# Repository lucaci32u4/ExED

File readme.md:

# Extended Digital Electronics laboratory

This laboratory is intended to be used as teaching material for the 6th Digital Electronics laboratory in the Faculty of Computer Science, Politehnica University of Bucharest.

This laboratory material presents the functioning of a shift register, a ring counter and a phase-locked loop. The following applications can be built:

 * A semaphore-like appliance using a ring counter
 * A clock divider
 * Phase-locked loop used to correct the pulse width of a fixed-frequency input signal
 * Clock multiplier bult using the phase-locked loop and clock divider
 * Linear feedback shift register - a random number generator using the shift register and XOR gate

## Version v0.1

A batch of 10 boards v0.01 were built. Seven of them were populated and tested in field, while three were kept for archieval purposes.

After teaching the extended laboratory to two groups, the following observations can be made:

 * Replace the XOR gate with a XNOR gate to eliminate the need to seed the LFSR. A XNOR gate would allow it to be self-seeding.
 * There are missing traces near the shift registers that need to be drawn. This issue was fixed by hand using wire on the first batch
 * Remove R36 to allow a much more dynamic range for the PLL.
 * Add LED to all clock inputs to allow better observation of the circuit.
 * Add reverse-polarity protection.

These flaws are planned to be fixed in version v0.2.

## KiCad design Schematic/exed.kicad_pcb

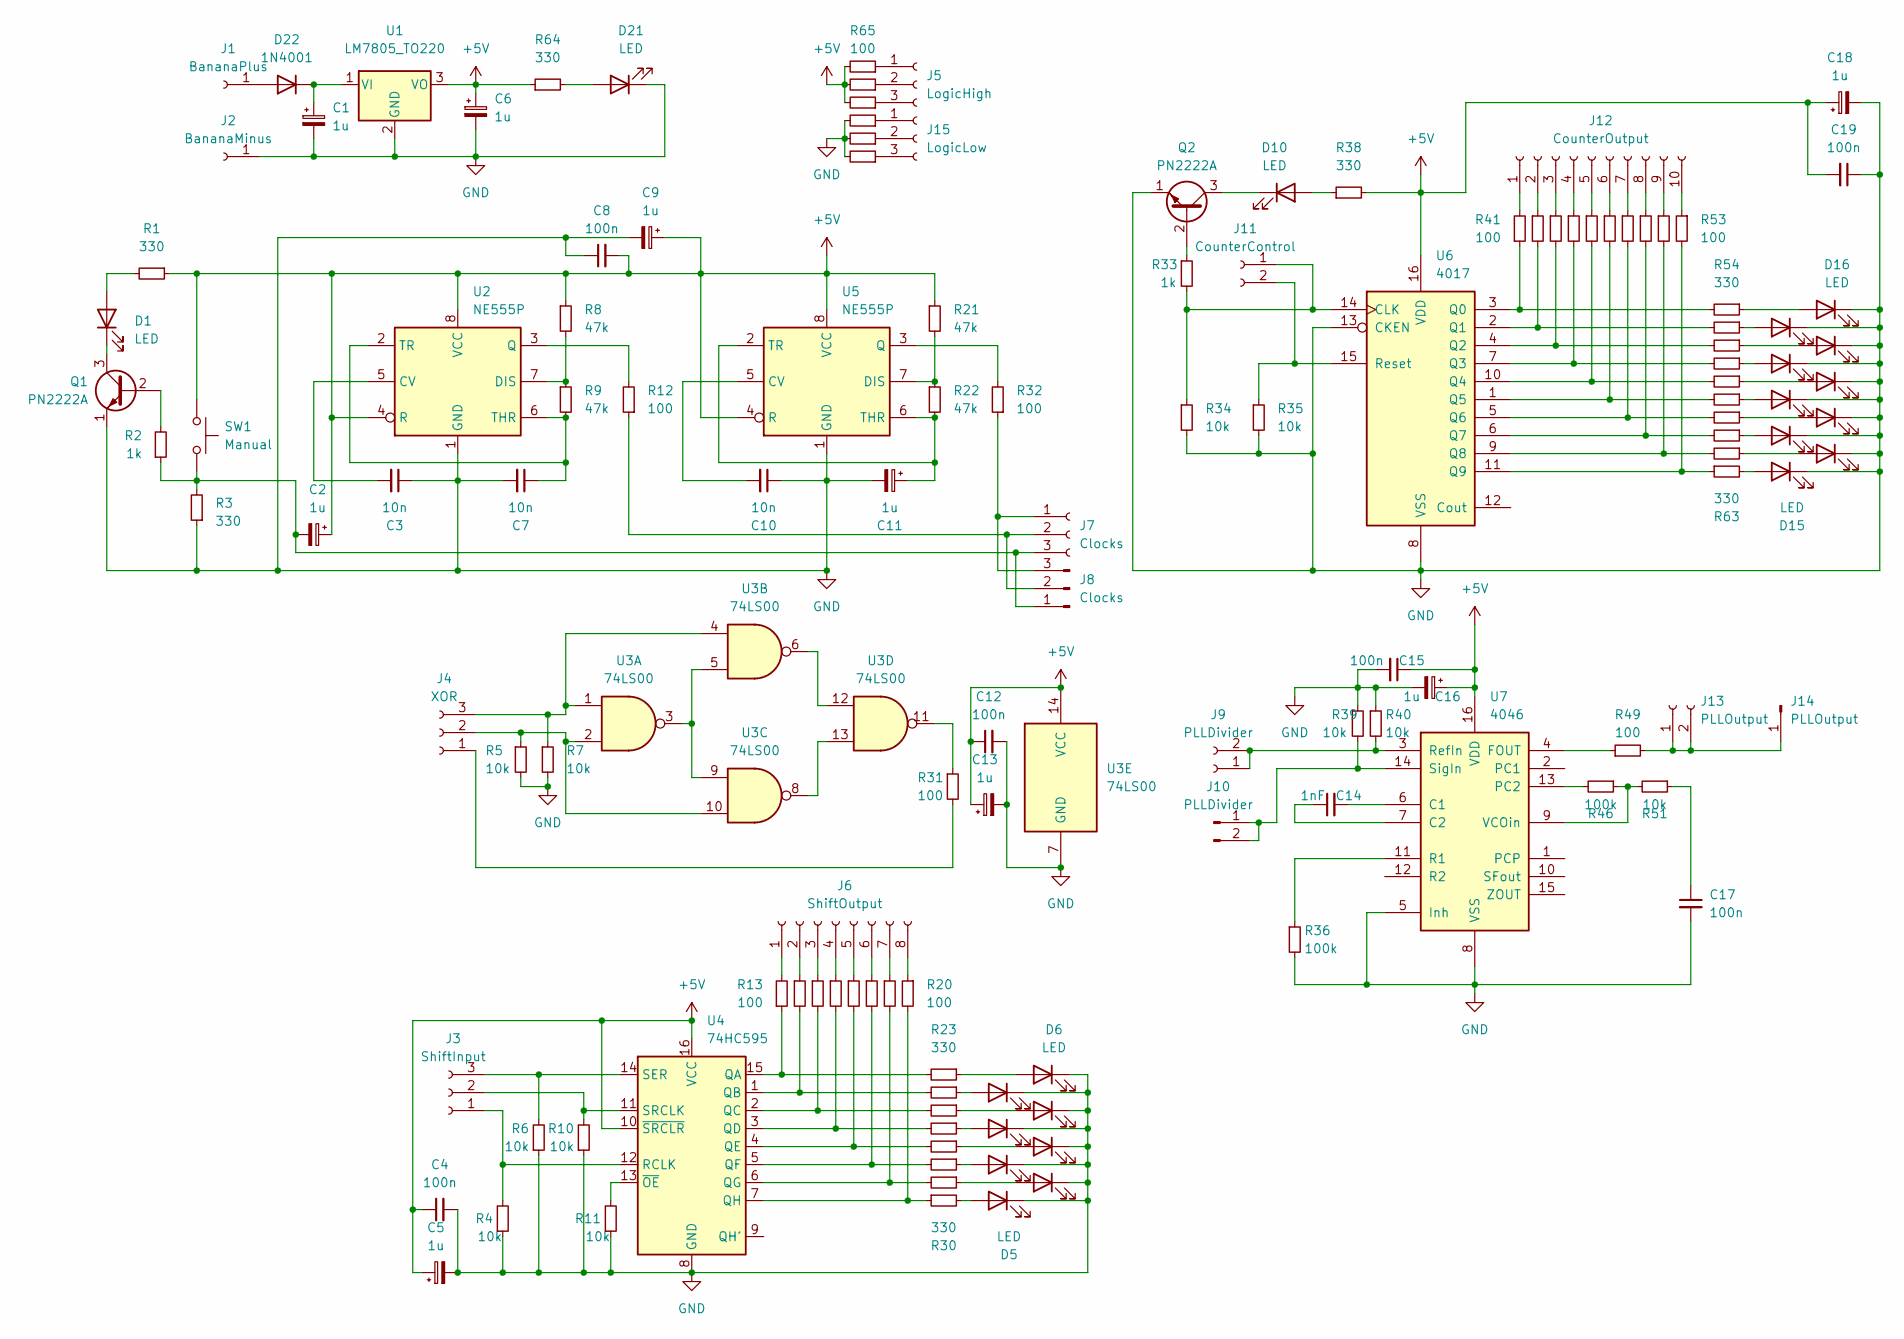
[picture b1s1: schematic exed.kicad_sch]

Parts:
C1, C2, C5, C6, C9, C11, C13, C16, C18: 1u; C_0603_1608Metric_Pad1.08x0.95mm_HandSolder
C3, C7, C10: 10n; C_0603_1608Metric_Pad1.08x0.95mm_HandSolder
C4, C8, C12, C15, C17, C19: 100n; C_0805_2012Metric_Pad1.18x1.45mm_HandSolder
C14: 1nF; C_0603_1608Metric_Pad1.08x0.95mm_HandSolder
D1, D2, D3, D4, D5, D6, D7, D8, D9, D10, D11, D12, D13, D14, D15, D16, D17, D18, D19, D20, D21: LED; LED_0603_1608Metric_Pad1.05x0.95mm_HandSolder
D22: 1N4001; D_DO-41_SOD81_P10.16mm_Horizontal
J1: BananaPlus; Banana_Jack_1Pin
J2: BananaMinus; Banana_Jack_1Pin
J3: ShiftInput; PinHeader_1x03_P2.54mm_Vertical
J4: XOR; PinHeader_1x03_P2.54mm_Vertical
J5: LogicHigh; PinHeader_1x03_P2.54mm_Vertical
J6: ShiftOutput; PinHeader_1x08_P2.54mm_Vertical
J7, J8: Clocks; PinHeader_1x03_P2.54mm_Vertical
J9, J10: PLLDivider; PinHeader_1x02_P2.54mm_Vertical
J11: CounterControl; PinHeader_1x02_P2.54mm_Vertical
J12: CounterOutput; PinHeader_1x10_P2.54mm_Vertical
J13: PLLOutput; PinHeader_1x02_P2.54mm_Vertical
J14: PLLOutput; PinHeader_1x01_P2.54mm_Vertical
J15: LogicLow; PinHeader_1x03_P2.54mm_Vertical
Q1, Q2: PN2222A; TO-92_Inline
R1, R3, R23, R24, R25, R26, R27, R28, R29, R30, R38, R54, R55, R56, R57, R58, R59, R60, R61, R62, R63, R64: 330; R_0603_1608Metric_Pad0.98x0.95mm_HandSolder
R2, R33: 1k; R_0603_1608Metric_Pad0.98x0.95mm_HandSolder
R4, R5, R6, R7, R10, R11, R34, R35, R39, R40, R51: 10k; R_0603_1608Metric_Pad0.98x0.95mm_HandSolder
R8, R9, R21, R22: 47k; R_0603_1608Metric_Pad0.98x0.95mm_HandSolder
R12, R13, R14, R15, R16, R17, R18, R19, R20, R31, R32, R41, R42, R43, R44, R45, R47, R48, R49, R50, R52, R53, R65, R66, R67, R68, R69, R70: 100; R_0603_1608Metric_Pad0.98x0.95mm_HandSolder
R36, R46: 100k; R_0603_1608Metric_Pad0.98x0.95mm_HandSolder
SW1: Manual; SW_PUSH_6mm
U1: LM7805_TO220; TO-220-3_Horizontal_TabDown
U2, U5: NE555P; DIP-8_W7.62mm
U3: 74LS00; DIP-14_W7.62mm
U4: 74HC595; DIP-16_W7.62mm
U6: 4017; DIP-16_W7.62mm
U7: 4046; DIP-16_W7.62mm

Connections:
+5V: C2.1, C4.1, C5.1, C6.1, C8.2, C9.1, C12.1, C13.1, C15.1, C16.1, C18.1, C19.2, R1.1, R8.1, R21.1, R38.2, R64.1, R65.2, R66.2, R67.2, SW1.1, U1.3 (VO), U2.4 (R), U2.8 (VCC), U3.14 (VCC), U4.10 (~SRCLR), U4.16 (VCC), U5.4 (R), U5.8 (VCC), U6.16 (VDD), U7.16 (VDD)
GND: C1.2, C3.1, C4.2, C5.2, C6.2, C7.2, C8.1, C9.2, C10.1, C11.2, C12.2, C13.2, C15.2, C16.2, C17.2, C18.2, C19.1, D2.1 (K), D3.1 (K), D4.1 (K), D5.1 (K), D6.1 (K), D7.1 (K), D8.1 (K), D9.1 (K), D11.1 (K), D12.1 (K), D13.1 (K), D14.1 (K), D15.1 (K), D16.1 (K), D17.1 (K), D18.1 (K), D19.1 (K), D20.1 (K), D21.1 (K), J2.1, Q1.1 (E), Q2.1 (E), R3.1, R4.1, R5.2, R6.1, R7.2, R10.1, R11.1, R34.2, R35.2, R36.2, R39.1, R40.1, R68.2, R69.2, R70.2, U1.2 (GND), U2.1 (GND), U3.7 (GND), U4.8 (GND), U5.1 (GND), U6.8 (VSS), U6.13 (CKEN), U7.5 (Inh), U7.8 (VSS)
unnamed: C17.1, R51.1
unnamed: D1.2 (A), R1.2
unnamed: D1.1 (K), Q1.3 (C)
unnamed: D2.2 (A), R24.1
unnamed: D3.2 (A), R26.1
unnamed: D4.2 (A), R28.1
unnamed: D5.2 (A), R30.2
unnamed: D6.2 (A), R23.1
unnamed: D7.2 (A), R25.1
unnamed: D8.2 (A), R27.1
unnamed: D9.2 (A), R29.1
unnamed: D10.2 (A), R38.1
unnamed: D10.1 (K), Q2.3 (C)
unnamed: D11.2 (A), R55.1
unnamed: D12.2 (A), R57.1
unnamed: D13.2 (A), R59.1
unnamed: D14.2 (A), R61.1
unnamed: D15.2 (A), R63.2
unnamed: D16.2 (A), R54.1
unnamed: D17.2 (A), R56.1
unnamed: D18.2 (A), R58.1
unnamed: D19.2 (A), R60.1
unnamed: D20.2 (A), R62.1
unnamed: D21.2 (A), R64.2
unnamed: D22.2 (A), J1.1
unnamed: C1.1, D22.1 (K), U1.1 (VI)
unnamed: J3.1, R4.2, U4.12 (RCLK)
unnamed: J3.2, R10.2, U4.11 (SRCLK)
unnamed: J3.3, R6.2, U4.14 (SER)
unnamed: J4.1, R31.2
unnamed: J4.2, R5.1, U3.2, U3.10
unnamed: J4.3, R7.1, U3.1, U3.4
unnamed: J5.1, R65.1
unnamed: J5.2, R66.1
unnamed: J5.3, R67.1
unnamed: J6.1, R13.2
unnamed: J6.2, R14.1
unnamed: J6.3, R15.1
unnamed: J6.4, R16.1
unnamed: J6.5, R17.1
unnamed: J6.6, R18.1
unnamed: J6.7, R19.1
unnamed: J6.8, R20.1
unnamed: J7.1, J8.3, R32.1
unnamed: J7.2, J8.2, R12.1
unnamed: C2.2, J7.3, J8.1, R2.1, R3.2, SW1.2
unnamed: J9.1, J9.2, R40.2, U7.3 (RefIn)
unnamed: J10.1, J10.2, R39.2, U7.14 (SigIn)
unnamed: J11.1, R33.2, R34.1, U6.14 (CLK)
unnamed: J11.2, R35.1, U6.15 (Reset)
unnamed: J12.1, R41.2
unnamed: J12.2, R42.1
unnamed: J12.3, R43.1
unnamed: J12.4, R44.1
unnamed: J12.5, R45.1
unnamed: J12.6, R47.1
unnamed: J12.7, R48.1
unnamed: J12.8, R50.1
unnamed: J12.9, R52.1
unnamed: J12.10, R53.1
unnamed: J13.1, J13.2, J14.1, R49.2
unnamed: J15.1, R68.1
unnamed: J15.2, R69.1
unnamed: J15.3, R70.1
unnamed: Q1.2 (B), R2.2
unnamed: Q2.2 (B), R33.1
unnamed: R31.1, U3.11
unnamed: C3.2, U2.5 (CV)
unnamed: R8.2, R9.1, U2.7 (DIS)
unnamed: R12.2, U2.3 (Q)
unnamed: C7.1, R9.2, U2.2 (TR), U2.6 (THR)
unnamed: U3.3, U3.5, U3.9
unnamed: U3.6, U3.12
unnamed: U3.8, U3.13
unnamed: R13.1, R23.2, U4.15 (QA)
unnamed: R14.2, R24.2, U4.1 (QB)
unnamed: R15.2, R25.2, U4.2 (QC)
unnamed: R16.2, R26.2, U4.3 (QD)
unnamed: R17.2, R27.2, U4.4 (QE)
unnamed: R18.2, R28.2, U4.5 (QF)
unnamed: R19.2, R29.2, U4.6 (QG)
unnamed: R20.2, R30.1, U4.7 (QH)
unnamed: R11.2, U4.13 (~OE)
unnamed: C10.2, U5.5 (CV)
unnamed: R21.2, R22.1, U5.7 (DIS)
unnamed: R32.2, U5.3 (Q)
unnamed: C11.1, R22.2, U5.2 (TR), U5.6 (THR)
unnamed: R41.1, R54.2, U6.3 (Q0)
unnamed: R42.2, R55.2, U6.2 (Q1)
unnamed: R43.2, R56.2, U6.4 (Q2)
unnamed: R44.2, R57.2, U6.7 (Q3)
unnamed: R45.2, R58.2, U6.10 (Q4)
unnamed: R47.2, R59.2, U6.1 (Q5)
unnamed: R48.2, R60.2, U6.5 (Q6)
unnamed: R50.2, R61.2, U6.6 (Q7)
unnamed: R52.2, R62.2, U6.9 (Q8)
unnamed: R53.2, R63.1, U6.11 (Q9)
unnamed: C14.2, U7.6 (C1)
unnamed: C14.1, U7.7 (C2)
unnamed: R49.1, U7.4 (FOUT)
unnamed: R46.2, U7.13 (PC2)
unnamed: R36.1, U7.11 (R1)
unnamed: R46.1, R51.2, U7.9 (VCOin)

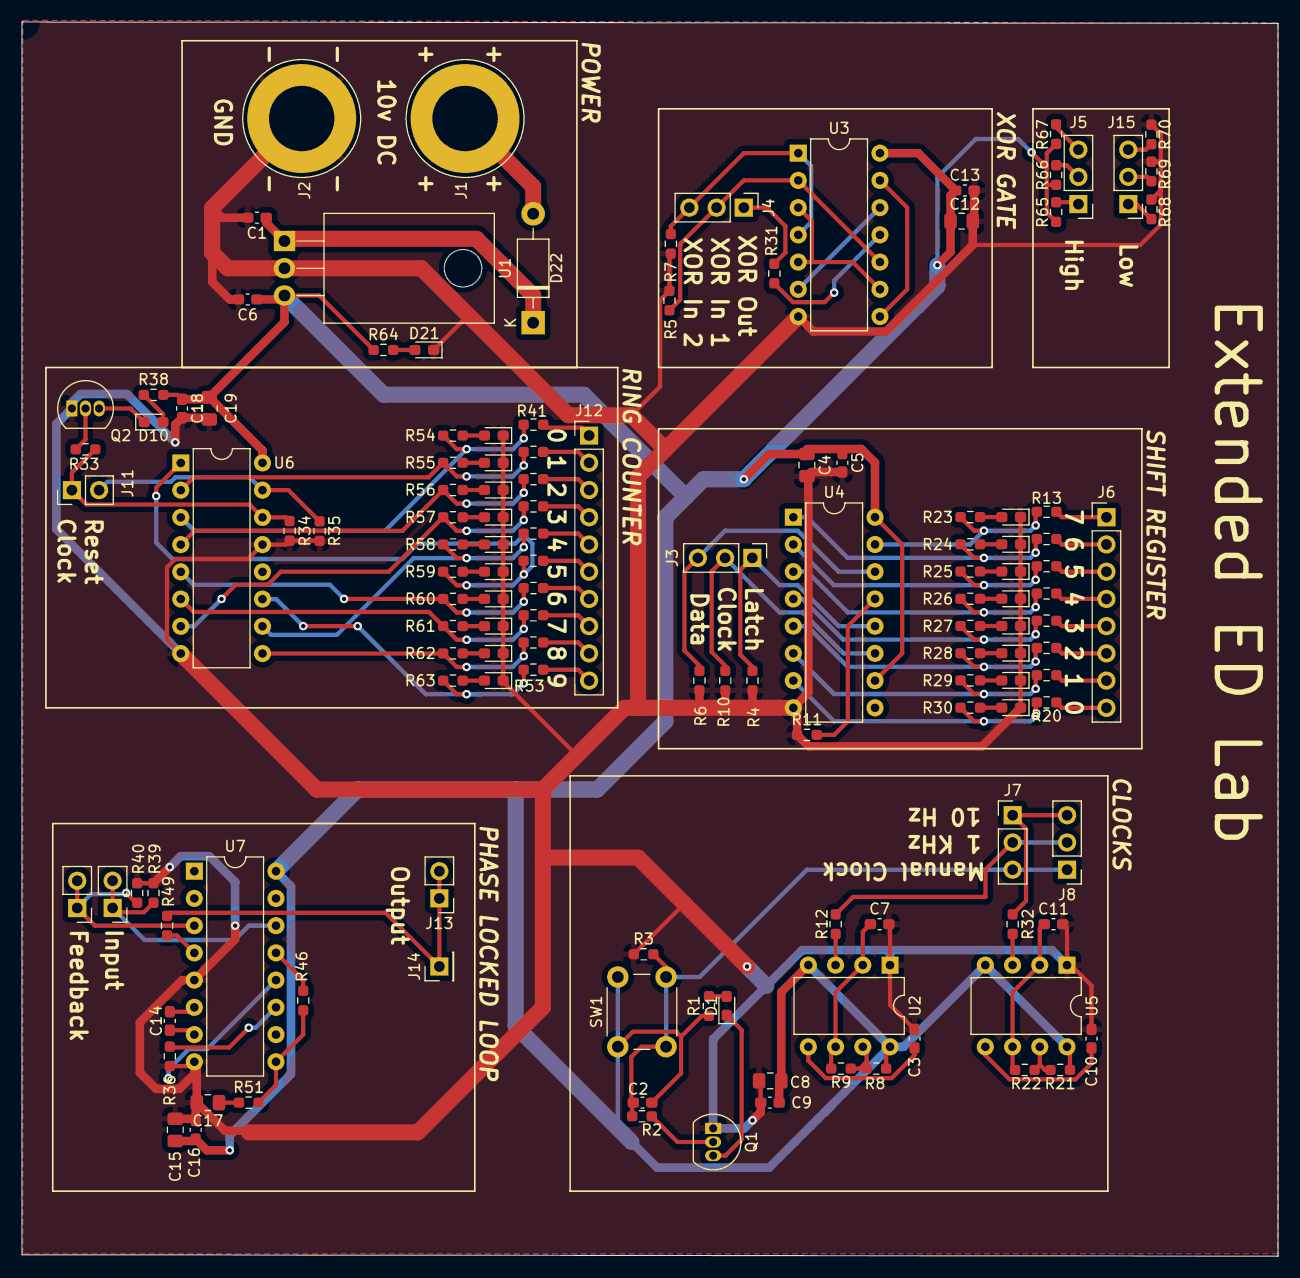
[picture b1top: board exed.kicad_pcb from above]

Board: 2 copper layers, 117.2 x 115.1 mm, 135 parts (0 on the bottom side), 105 nets.

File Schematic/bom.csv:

Id,Designator,Package,Quantity,Designation,Supplier and ref,
1,"R60,R58,R28,R64,R56,R55,R30,R38,R24,R57,R26,R54,R59,R61,R27,R63,R29,R25,R62,R23,R1",R_0603_1608Metric_Pad0.98x0.95mm_HandSolder,21,330,2861870,
2,D22,D_DO-41_SOD81_P10.16mm_Horizontal,1,1N4001,1458986,
3,J11,PinHeader_1x02_P2.54mm_Vertical,1,CounterControl,,
4,U6,DIP-16_W7.62mm,1,4017,3006265,
5,"R2,R33",R_0603_1608Metric_Pad0.98x0.95mm_HandSolder,2,1k,9233385,
6,U1,TO-220-3_Horizontal_TabDown,1,LM7805_TO220,9666095,
7,"D4,D11,D5,D17,D2,D7,D13,D16,D1,D10,D18,D9,D8,D14,D19,D3,D15,D12,D6,D21,D20",LED_0603_1608Metric_Pad1.05x0.95mm_HandSolder,21,LED,2687486,
8,"C17,C19,C4,C12,C15,C8",C_0805_2012Metric_Pad1.18x1.45mm_HandSolder,6,100n,1414615,
9,U4,DIP-16_W7.62mm,1,74HC595,3120865,
10,J4,PinHeader_1x03_P2.54mm_Vertical,1,XOR,,
11,"J7,J8",PinHeader_1x03_P2.54mm_Vertical,2,Clocks,,
12,"R12,R32,R49,R31,R65,R16,R53,R18,R17,R42,R43,R52,R47,R68,R13,R41,R48,R66,R45,R14,R20,R15,R67,R50,R70,R44,R19,R69",R_0603_1608Metric_Pad0.98x0.95mm_HandSolder,28,100,9233253,
13,J3,PinHeader_1x03_P2.54mm_Vertical,1,ShiftInput,,
14,"C13,C6,C1,C9,C11,C5,C16,C18,C2",CP_Radial_D4.0mm_P2.00mm,9,1u,9452524,changed to 0603 code 1658868
15,U7,DIP-16_W7.62mm,1,4046,3123331,
16,"U5,U2",DIP-8_W7.62mm,2,NE555P,3006909,
17,J12,PinHeader_1x10_P2.54mm_Vertical,1,CounterOutput,,
18,"Q1,Q2",TO-92_Inline,2,PN2222A,1700711,
19,J14,PinHeader_1x01_P2.54mm_Vertical,1,PLLOutput,,
20,J15,PinHeader_1x03_P2.54mm_Vertical,1,LogicLow,,
21,J2,Banana_Jack_1Pin,1,BananaMinus,,
22,J1,Banana_Jack_1Pin,1,BananaPlus,,
23,J6,PinHeader_1x08_P2.54mm_Vertical,1,ShiftOutput,,
24,"R51,R11,R6,R4,R7,R34,R40,R35,R39,R5,R10",R_0603_1608Metric_Pad0.98x0.95mm_HandSolder,11,10k,2008360,
25,"J10,J9",PinHeader_1x02_P2.54mm_Vertical,2,PLLDivider,,
26,"C7,C3,C10",C_1206_3216Metric_Pad1.33x1.80mm_HandSolder,3,10n,491202,changed to 0603 code 722236
27,J5,PinHeader_1x03_P2.54mm_Vertical,1,LogicHigh,,
28,SW1,SW_PUSH_6mm,1,Manual,,
29,U3,DIP-14_W7.62mm,1,74LS00,3120419,
30,J13,PinHeader_1x02_P2.54mm_Vertical,1,PLLOutput,,
31,"R9,R22,R8,R21",R_0603_1608Metric_Pad0.98x0.95mm_HandSolder,4,47k,1652881,
32,"R46,R36",R_0603_1608Metric_Pad0.98x0.95mm_HandSolder,2,100k,9233628,
33,R37,R_0603_1608Metric_Pad0.98x0.95mm_HandSolder,1,10M,2446549,
34,C14,C_0603_1608Metric_Pad1.08x0.95mm_HandSolder,1,1nF,1740627,
35,R3,R_0603_1608Metric_Pad0.98x0.95mm_HandSolder,1,500,,// TODO: replace with 330 ohm

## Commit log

2022-06-23 Add schematic prototype and pcb
2022-06-26 Changed footprint of electrolytic to smd 0603
2022-06-27 Added logo and bumped version
2023-06-05 Final version v0.1

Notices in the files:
Schematic/exed.kicad_pcb:
Licensed under GPL v3
